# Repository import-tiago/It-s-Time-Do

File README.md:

# It's Time, Do!

__It's Time, Do!__ is a system (hardware + firmware + web application) to control over the internet the on/off or programming to automatically run other devices and electronic equipments.

The inspiration for creating this project comes from the need to schedule my ~~not smart~~ washing machine to auto-start when I'm out and about to save time and just put the clothes to dry when I get home.

## Push Notifications
The hardware device can trigger a web push notification to notify web clients of tasks that have started or ended (either previously scheduled tasks or even tasks that have been started locally).

|  |  |
|--|--|
  
 ## Task History and Instant Data
 Through Firebase's Real Time Database (RTDB), it is possible to monitor instant __It's Time, Do!__ hardware device parameters, such as local date, local time, status of the scheduled task and current firmware version; as well as status of the device being controlled (in my case, the washing machine), whether or not it is working, log of all previous tasks with start and finished date and time of each one.

## Hardware / Circuit Diagram
Controller: [M5StickC PLUS](https://docs.m5stack.com/en/core/m5stickc_plus) - [M5Stack Official Store](https://pt.aliexpress.com/item/1005003297502591.html?spm=a2g0o.order_list.order_list_main.10.3023caa4s3zJPO&gatewayAdapt=glo2bra)<br/>
Module: [Unit Relay](https://docs.m5stack.com/en/unit/relay) - [M5Stack Official Store](https://pt.aliexpress.com/item/1005003299262655.html?spm=a2g0o.order_list.order_list_main.11.3023caa4s3zJPO&gatewayAdapt=glo2bra)

### Contributing
0. Give this project a :star:
1. Create an issue and describe your idea.
2. [Fork it](https://github.com/import-tiago/It-s-Time-Do/fork).
3. Create your feature branch (`git checkout -b my-new-feature`).
4. Commit your changes (`git commit -a -m "Added feature title"`).
5. Publish the branch (`git push origin my-new-feature`).
6. Create a new pull request.
7. Done! :heavy_check_mark:

### License Information
<br /><span xmlns:dct="http://purl.org/dc/terms/" property="dct:title">It's Time, Do!</span> by <a xmlns:cc="http://creativecommons.org/ns#" href="https://twitter.com/import_tiago" property="cc:attributionName" rel="cc:attributionURL">Tiago Silva</a> is licensed under a <a rel="license" href="http://creativecommons.org/licenses/by-nc-sa/4.0/">Creative Commons Attribution-NonCommercial-ShareAlike 4.0 International License</a>.

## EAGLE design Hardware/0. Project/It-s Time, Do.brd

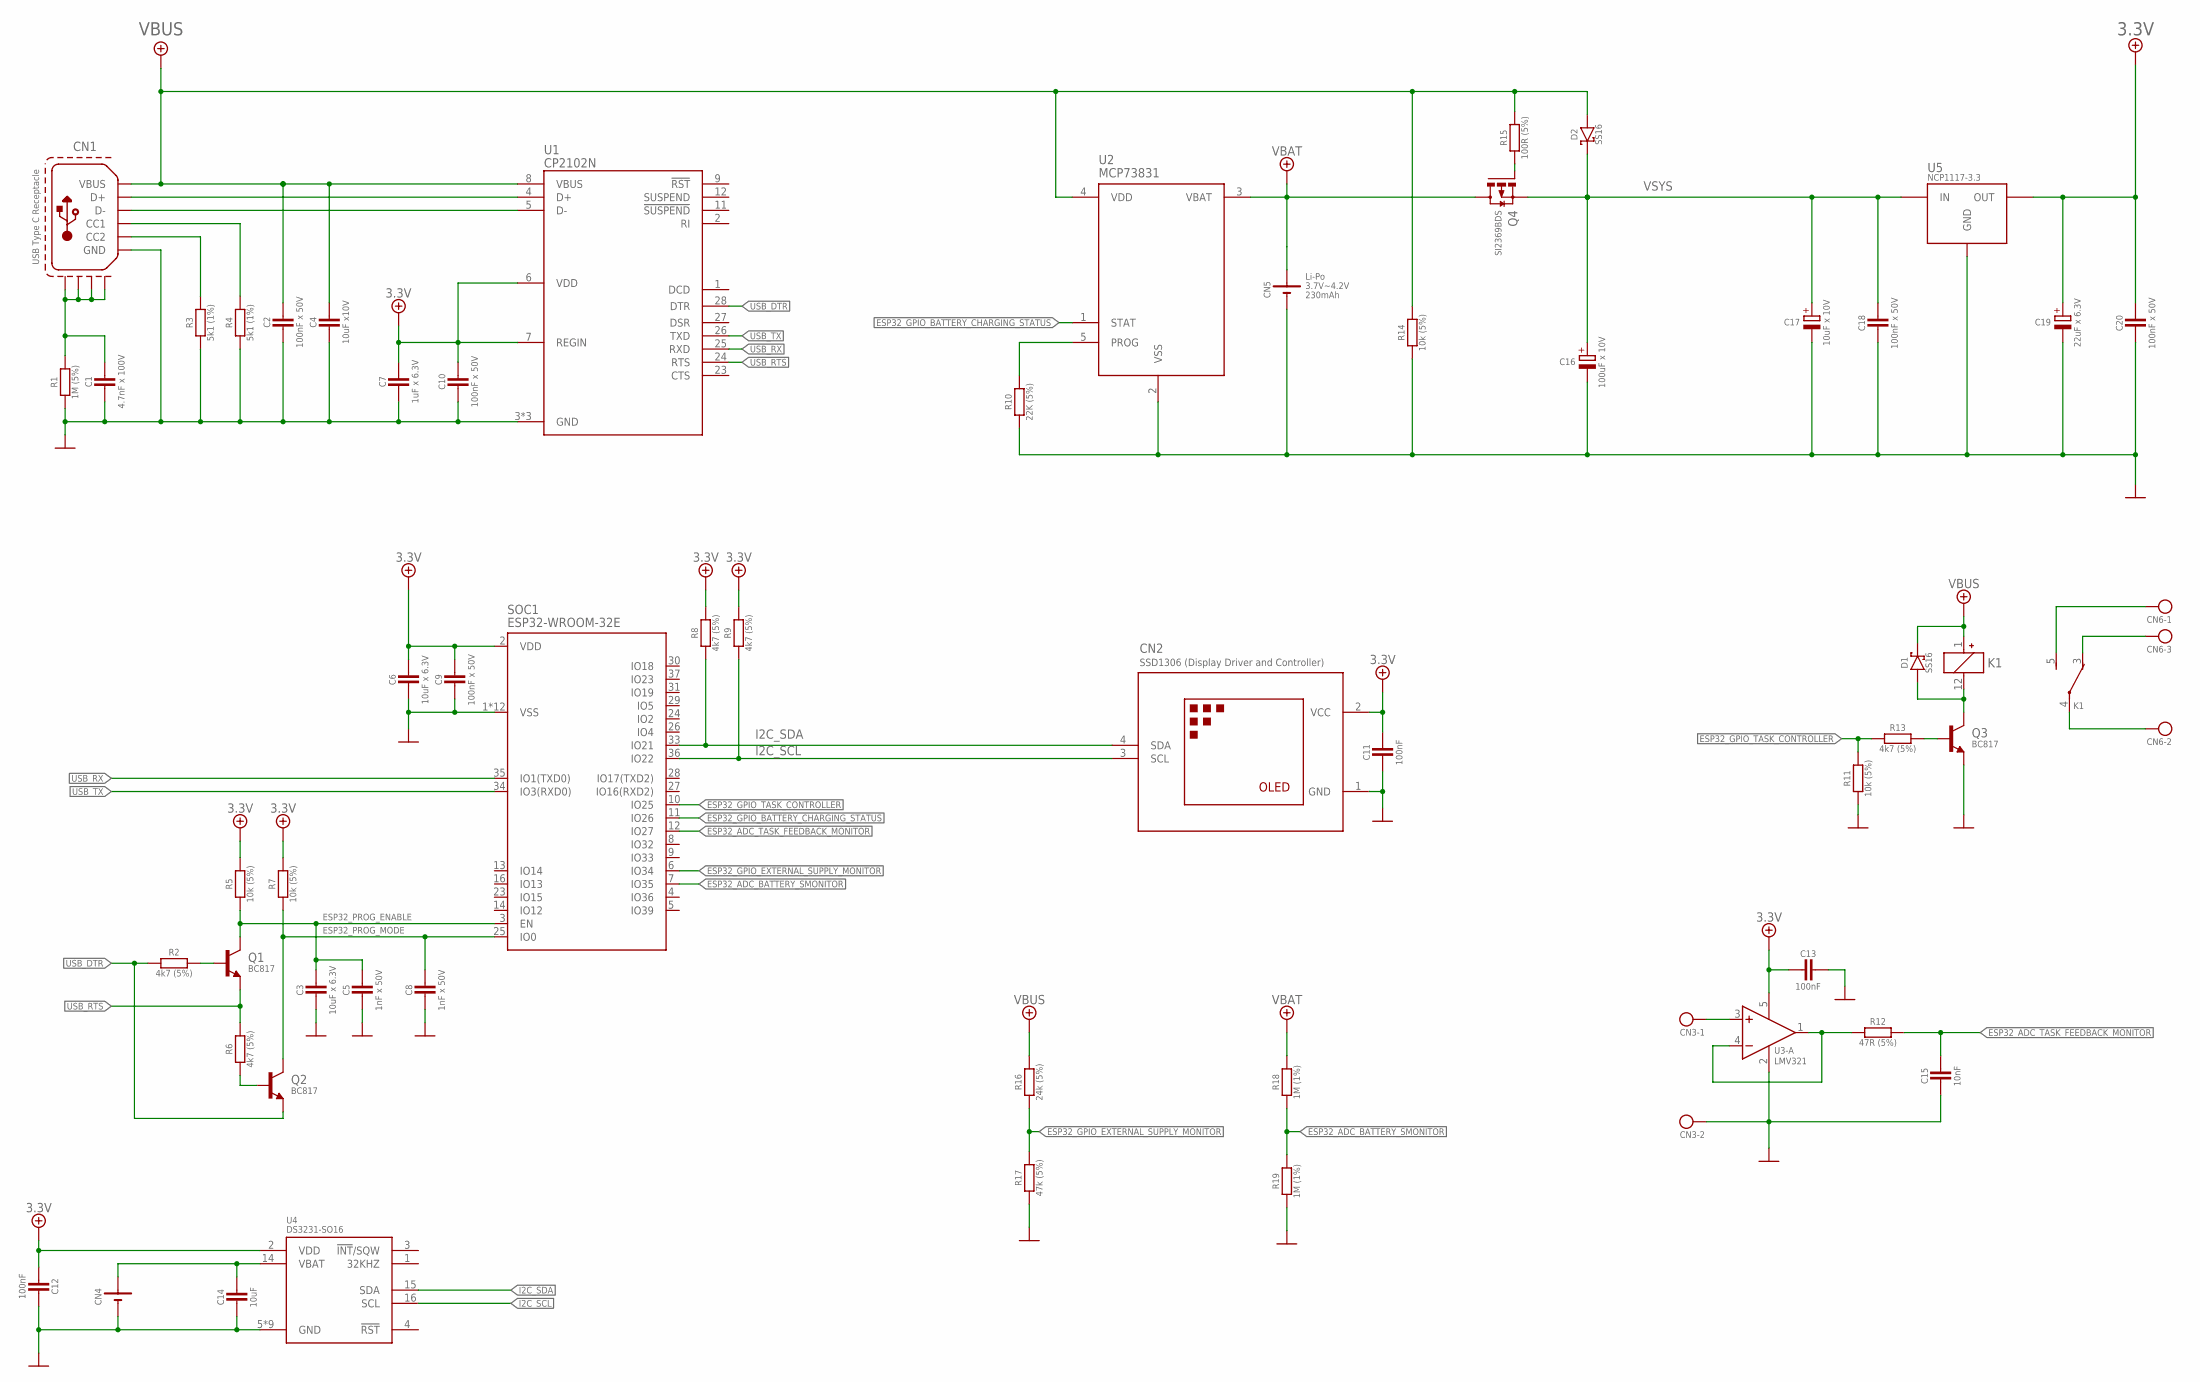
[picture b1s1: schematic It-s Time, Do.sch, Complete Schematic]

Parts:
C1: 4.7nF x 100V; C0603
C2, C9, C10, C18, C20: 100nF x 50V; C0603
C3, C6: 10uF x 6.3V; C0603
C4: 10uF x10V; C0603
C5, C8: 1nF x 50V; C0603
C7: 1uF x 6.3V; C0603
C11, C12, C13: 100nF; C0603; PARTNO *
C14: 10uF; C0603; PARTNO GRJ155R60J106ME11D
C15: 10nF; C0603
C16: 100uF x 10V; PTH-5MM
C17: 10uF x 10V; C1206_POL
C19: 22uF x 6.3V; C1206_POL
CN1: USB Type C Receptacle; USB-C-16P-2LAYER-PADS
CN2: OLED-MODULE-I2C-SOCKET; PIN_HEADER_1X4_FEMALE
CN3: 2P-MINI-FIT-JR; MINI-FIT-JR-2P
CN4: CR1220; CR1220/1225_HOLDER2; PARTNO *
CN5: BATTERY; JST-PH-2P-H; VOLTAGE 3.7V~4.2V
CN6: 3P-MINI-FIT-JR; MINI-FIT-JR-3P
D1: FM4004; DO-214AC
D2: SCHOTTKY-SS16; DO-214AC
K1: DPDT-SMD; EE2-5NU
Q1, Q2: NPN-BC817; SOT23-3
Q3: BC817; SOT23-3
Q4: P-FET-ENHANCEMENT-SI2369BDS; SOT23-3
R1: 1M (5%); R0603
R2, R6, R8, R9, R13: 4k7 (5%); R0603
R3, R4: 5k1 (1%); R0603
R5, R7, R11, R14: 10k (5%); R0603
R10: 22K (5%); R0603; PARTNO *
R12: 47R (5%); R0603
R15: 100R (5%); R0603
R16: 24k (5%); R0603; PARTNO RC0402FR-0724KL
R17: 47k (5%); R0603; PARTNO RC0402FR-0747KL
R18, R19: 1M (1%); R0603; PARTNO *
SOC1: ESP32-WROOM-32E
U1: CP2102N; QFN-28
U2: MCP73831; SOT-23-5; PARTNO *
U3: LMV321; SOT-23-5
U4: DS3231-SO16; SOIC-16W_(SO16)
U5: 1117-3.3V; SOT-223-3

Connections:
0V: C1.1, C2.1, C3.2, C4.1, C5.2, C6.2, C7.1, C8.2, C9.2, C10.1, C11.2, C12.1, C13.1, C14.2, C15.2, C16.2 (-), C17.2 (-), C18.2, C19.2 (-), C20.2, CN1.GND, CN1.GND2 (GND), CN2.1 (GND), CN3.2, CN4.2 (-), CN5.2 (-), Q3.2 (E), R1.2, R3.2, R4.2, R10.1, R11.2, R14.1, R17.2, R19.1, SOC1.1 (VSS), SOC1.15 (VSS), SOC1.38 (VSS), SOC1.E1 (VSS), SOC1.E2 (VSS), SOC1.E3 (VSS), SOC1.E4 (VSS), SOC1.E5 (VSS), SOC1.E6 (VSS), SOC1.E7 (VSS), SOC1.E8 (VSS), SOC1.E9 (VSS), U1.3 (GND), U1.EXP (GND), U1.M (GND), U2.2 (VSS), U3.2 (V-), U4.5 (GND), U4.6 (GND), U4.7 (GND), U4.8 (GND), U4.9 (GND), U4.10 (GND), U4.11 (GND), U4.12 (GND), U4.13 (GND), U5.1 (GND)
3.3V: C6.1, C7.2, C9.1, C10.2, C11.1, C12.2, C13.2, C19.1 (+), C20.1, CN2.2 (VCC), R5.1, R7.1, R8.2, R9.2, SOC1.2 (VDD), U1.6 (VDD), U1.7 (REGIN), U3.5 (V+), U4.2 (VDD), U5.2 (OUT), U5.4 (OUT)
ESP32_ADC_BATTERY_SMONITOR: R18.1, R19.2, SOC1.7 (IO35)
ESP32_ADC_TASK_FEEDBACK_MONITOR: C15.1, R12.2, SOC1.12 (IO27)
ESP32_GPIO_BATTERY_CHARGING_STATUS: SOC1.11 (IO26), U2.1 (STAT)
ESP32_GPIO_EXTERNAL_SUPPLY_MONITOR: R16.2, R17.1, SOC1.6 (IO34)
ESP32_GPIO_TASK_CONTROLLER: R11.1, R13.2, SOC1.10 (IO25)
ESP32_PROG_ENABLE: C3.1, C5.1, Q1.3 (C), R5.2, SOC1.3 (EN)
ESP32_PROG_MODE: C8.1, Q2.3 (C), R7.2, SOC1.25 (IO0)
I2C_SCL: CN2.3 (SCL), R9.1, SOC1.36 (IO22), U4.16 (SCL)
I2C_SDA: CN2.4 (SDA), R8.1, SOC1.33 (IO21), U4.15 (SDA)
unnamed: CN1.B5 (CC2), R3.1
unnamed: CN1.A5 (CC1), R4.1
unnamed: CN1.A7 (D-), CN1.B7 (D-), U1.5 (D-)
unnamed: CN3.1, U3.3 (+IN)
unnamed: CN6.1, K1.5 (NO)
unnamed: CN1.A6 (D+), CN1.B6 (D+), U1.4 (D+)
unnamed: Q1.1 (B), R2.1
unnamed: Q2.1 (B), R6.1
unnamed: Q4.1 (G), R15.2
unnamed: R12.1, U3.1 (OUT), U3.4 (-IN)
unnamed: CN6.2, K1.4 (COM)
unnamed: CN6.3, K1.3 (NC)
unnamed: R10.2, U2.5 (PROG)
unnamed: Q3.1 (B), R13.1
unnamed: D1.2 (A), K1.12 (-), Q3.3 (C)
unnamed: C1.2, CN1.SHLD1 (S1), CN1.SHLD2 (S2), CN1.SHLD3 (S3), CN1.SHLD4 (S4), R1.1
P$1: CN5.1 (+), Q4.3 (D), R18.2, U2.3 (VBAT)
RTC_VBAT: C14.1, CN4.1 (+), U4.14 (VBAT)
USB_DTR: Q2.2 (E), R2.2, U1.28 (DTR)
USB_RTS: Q1.2 (E), R6.2, U1.24 (RTS)
USB_RX: SOC1.35 (IO1(TXD0)), U1.25 (RXD)
USB_TX: SOC1.34 (IO3(RXD0)), U1.26 (TXD)
VBUS: C2.2, C4.2, CN1.VBUS1 (VBUS), CN1.VBUS2 (VBUS), D1.1 (K), D2.2 (A), K1.1 (+), R14.2, R15.1, R16.1, U1.8 (VBUS), U2.4 (VDD)
VSYS: C16.1 (+), C17.1 (+), C18.1, D2.1 (K), Q4.2 (S), U5.3 (IN)

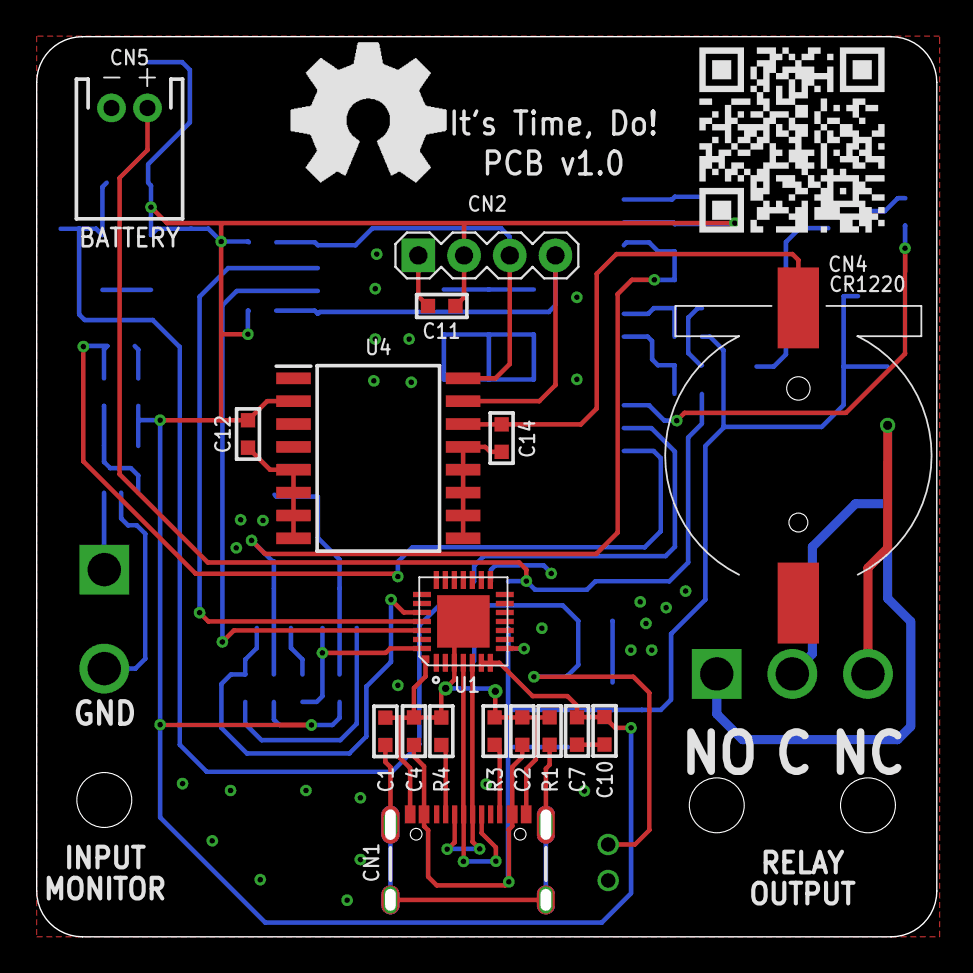
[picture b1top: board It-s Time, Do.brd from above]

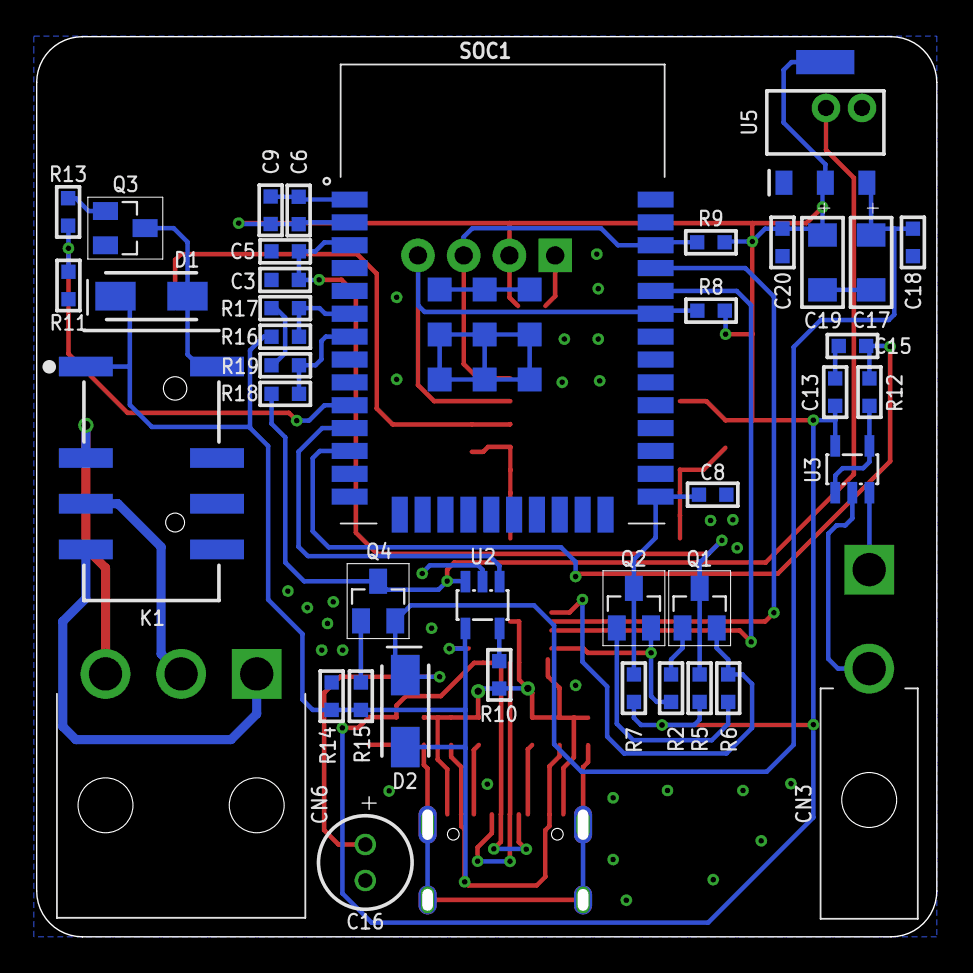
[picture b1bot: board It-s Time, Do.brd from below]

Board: 2 copper layers, 50.0 x 50.0 mm, 58 parts (41 on the bottom side), 35 nets.

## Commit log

2022-04-17 bug fix in 'last task duration' calc
2022-04-17 Added 'firmware version' in OLED home screen
2022-04-22 Web App + Push Notifications from Hardware Device trigger added
2022-04-24 Allows task duration monitor/log works from local or remote START trigger
2022-04-24 Web push notifications trigger from init and finished task on hardware device
2022-04-25 Firmware v1.4 release
2022-04-26 Minor improvements
2022-04-27 firmware v1.4.1 release
2022-04-27 firmware v1.4.2 release (bug fix)
2022-05-01 Firmware v1.6 release
2022-05-01 Minor improvements (just clean code)
2022-05-02 Add examples for auth secrets libs
2022-05-07 Firmware v1.7 release
2022-05-08 Firmware v1.8 release
2022-05-09 Firmware v1.8.1 release
2022-05-13 Firmware v1.9 release
2022-05-15 Schematic WIP
2022-05-15 Schematic v1.0 release
2022-05-15 New assets added
2022-05-15 Board design WIP
2022-05-16 Schematic v1.1 release
    - Minor improvements on parts designators position;
    - Just one resistor as pull up in not used pins at OLED display.
2022-05-26 Firmware v1.10 release
    - 'Firebase-ESP32' library updated from v3.3.2 to v3.3.6.
    - 'RTClib' library updated from v2.0.2 to v2.0.3.
2022-06-05 Firmware v1.11 release
2022-06-18 PCB v1.0 release
2022-07-02 Firmware v1.12 release
    - Fixed espressif32 platform at v3.5.0 because mbedtls (associated function) seems to have broken a bunch of libraries using it in the new versions.
2022-09-20 Firmware v1.13 release
2022-10-06 WebApp WIP
2022-11-21 Adjust layout to smartphone
2022-11-22 Finished
2023-03-26 M5StickC PLUS set as official new hardware (WIP)
2023-04-07 new feature: LCD auto turns-off after 1 min of inactivity (LCD life saving)
2023-04-08 new images added
2023-04-08 image resized
2023-04-09 added gnd ref to the circuit
2023-04-11 bug fix
2023-04-13 circuit design improved
2023-07-21 usernames in URLs updated
2023-11-26 FW v2.1 release
    - RTC IC from M5StickC Plus auto-update from NTP server after successfully Wi-Fi connection.
    - RSSI and Wi-Fi quality stability improved.
